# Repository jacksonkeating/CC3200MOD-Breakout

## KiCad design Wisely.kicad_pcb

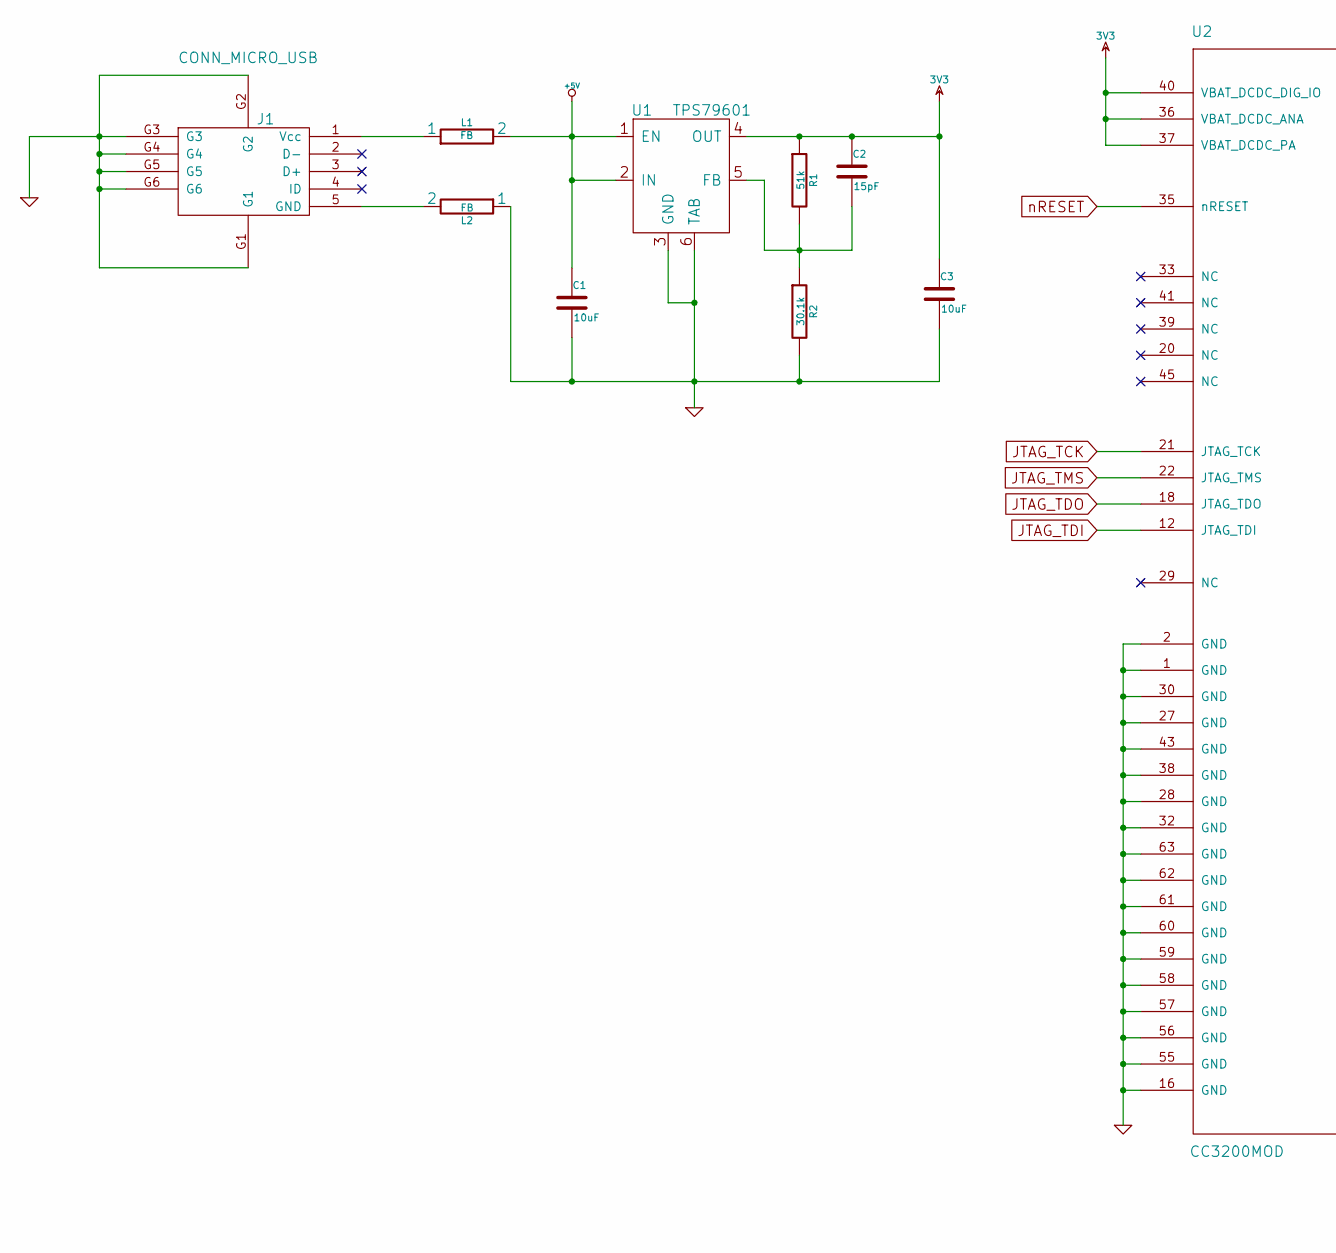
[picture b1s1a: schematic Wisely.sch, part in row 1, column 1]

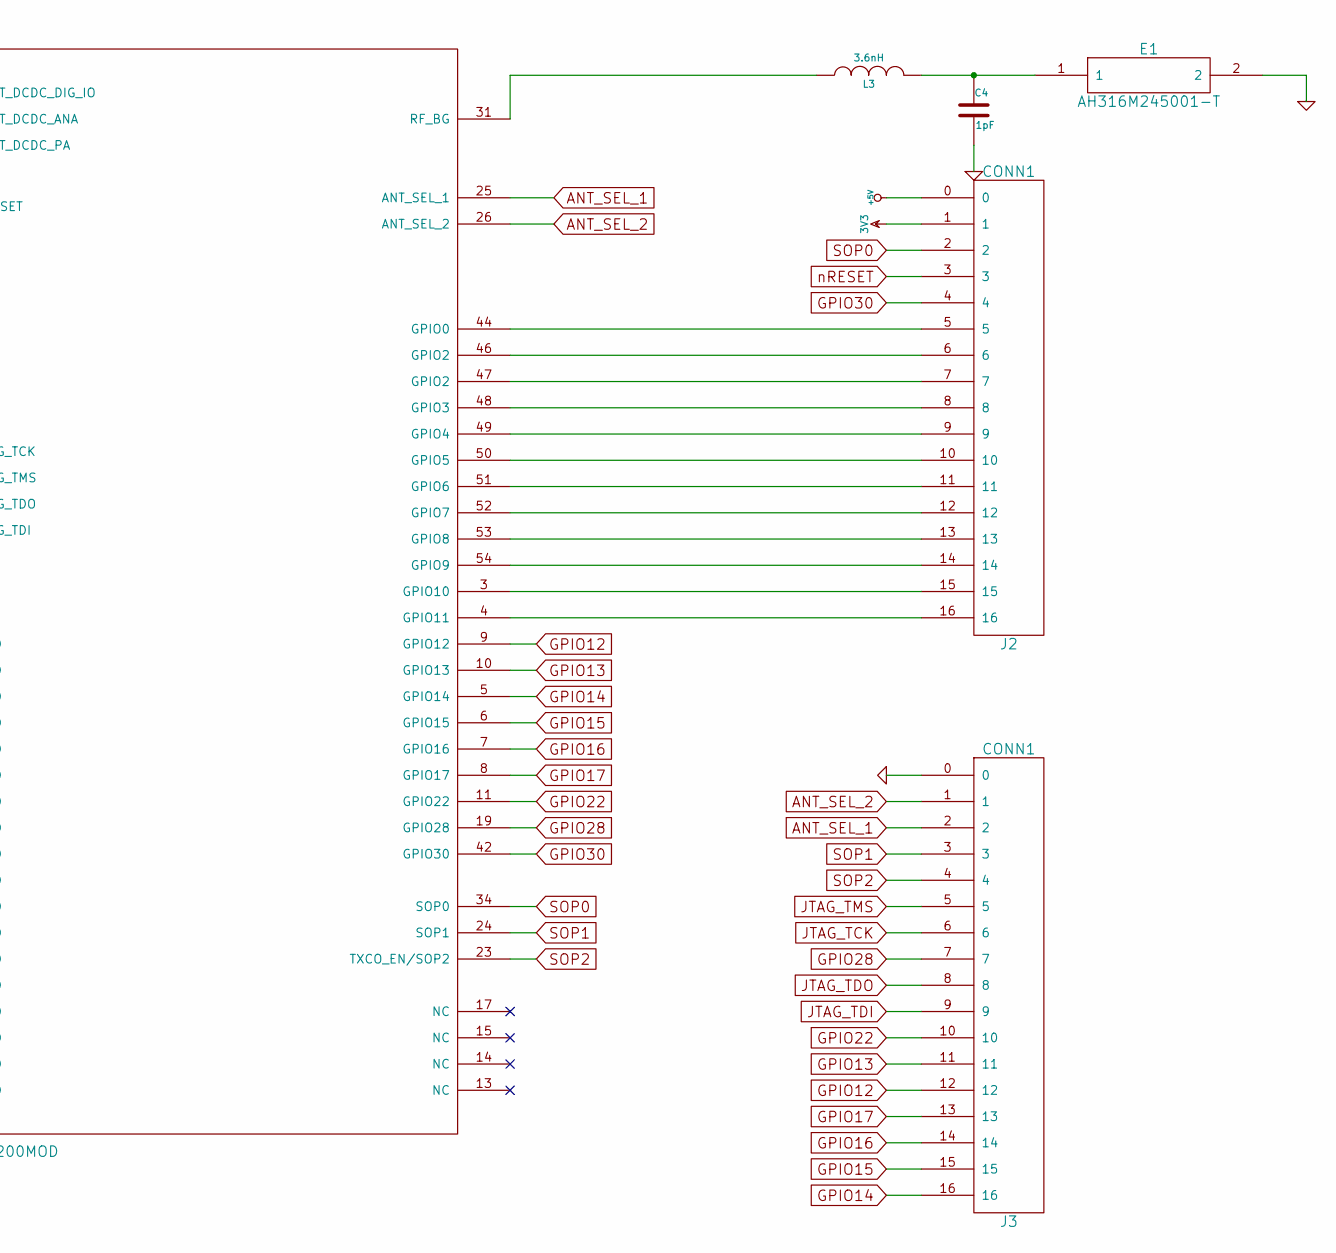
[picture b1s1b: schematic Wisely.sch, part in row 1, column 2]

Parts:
C1, C3: 10uF
C2: 15pF
C4: 1pF
E1: AH316M245001-T
J1: CONN_MICRO_USB
J2, J3: CONN1
L1, L2: FB
L3: 3.6nH
R1: 51k
R2: 30.1k
U1: TPS79601; Mfr_Part_Number TPS79601DCQR
U2: CC3200MOD

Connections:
3V3: C2.1, C3.1, J2.1, R1.1, U1.4 (OUT), U2.36 (VBAT_DCDC_ANA), U2.37 (VBAT_DCDC_PA), U2.40 (VBAT_DCDC_DIG_IO)
+5V: C1.1, J2.0, L1.2, U1.1 (EN), U1.2 (IN)
ANT_SEL_1: J3.2, U2.25 (ANT_SEL_1)
ANT_SEL_2: J3.1, U2.26 (ANT_SEL_2)
GND: C1.2, C3.2, C4.2, E1.2, J1.G1, J1.G2, J1.G3, J1.G4, J1.G5, J1.G6, J3.0, L2.1, R2.2, U1.3 (GND), U1.6 (TAB), U2.1 (GND), U2.2 (GND), U2.16 (GND), U2.27 (GND), U2.28 (GND), U2.30 (GND), U2.32 (GND), U2.38 (GND), U2.43 (GND), U2.55 (GND), U2.56 (GND), U2.57 (GND), U2.58 (GND), U2.59 (GND), U2.60 (GND), U2.61 (GND), U2.62 (GND), U2.63 (GND)
GPIO12: J3.12, U2.9 (GPIO12)
GPIO13: J3.11, U2.10 (GPIO13)
GPIO14: J3.16, U2.5 (GPIO14)
GPIO15: J3.15, U2.6 (GPIO15)
GPIO16: J3.14, U2.7 (GPIO16)
GPIO17: J3.13, U2.8 (GPIO17)
GPIO22: J3.10, U2.11 (GPIO22)
GPIO28: J3.7, U2.19 (GPIO28)
GPIO30: J2.4, U2.42 (GPIO30)
JTAG_TCK: J3.6, U2.21 (JTAG_TCK)
JTAG_TDI: J3.9, U2.12 (JTAG_TDI)
JTAG_TDO: J3.8, U2.18 (JTAG_TDO)
JTAG_TMS: J3.5, U2.22 (JTAG_TMS)
unnamed: J1.1 (Vcc), L1.1
unnamed: J1.5 (GND), L2.2
unnamed: C2.2, R1.2, R2.1, U1.5 (FB)
unnamed: L3.1, U2.31 (RF_BG)
unnamed: J2.7, U2.47 (GPIO2)
unnamed: J2.9, U2.49 (GPIO4)
unnamed: J2.8, U2.48 (GPIO3)
unnamed: J2.12, U2.52 (GPIO7)
unnamed: J2.11, U2.51 (GPIO6)
unnamed: J2.10, U2.50 (GPIO5)
unnamed: J2.14, U2.54 (GPIO9)
unnamed: J2.6, U2.46 (GPIO2)
unnamed: J2.5, U2.44 (GPIO0)
unnamed: J2.13, U2.53 (GPIO8)
unnamed: J2.16, U2.4 (GPIO11)
unnamed: J2.15, U2.3 (GPIO10)
unnamed: C4.1, E1.1, L3.2
SOP0: J2.2, U2.34 (SOP0)
SOP1: J3.3, U2.24 (SOP1)
SOP2: J3.4, U2.23 (TXCO_EN/SOP2)
nRESET: J2.3, U2.35 (nRESET)

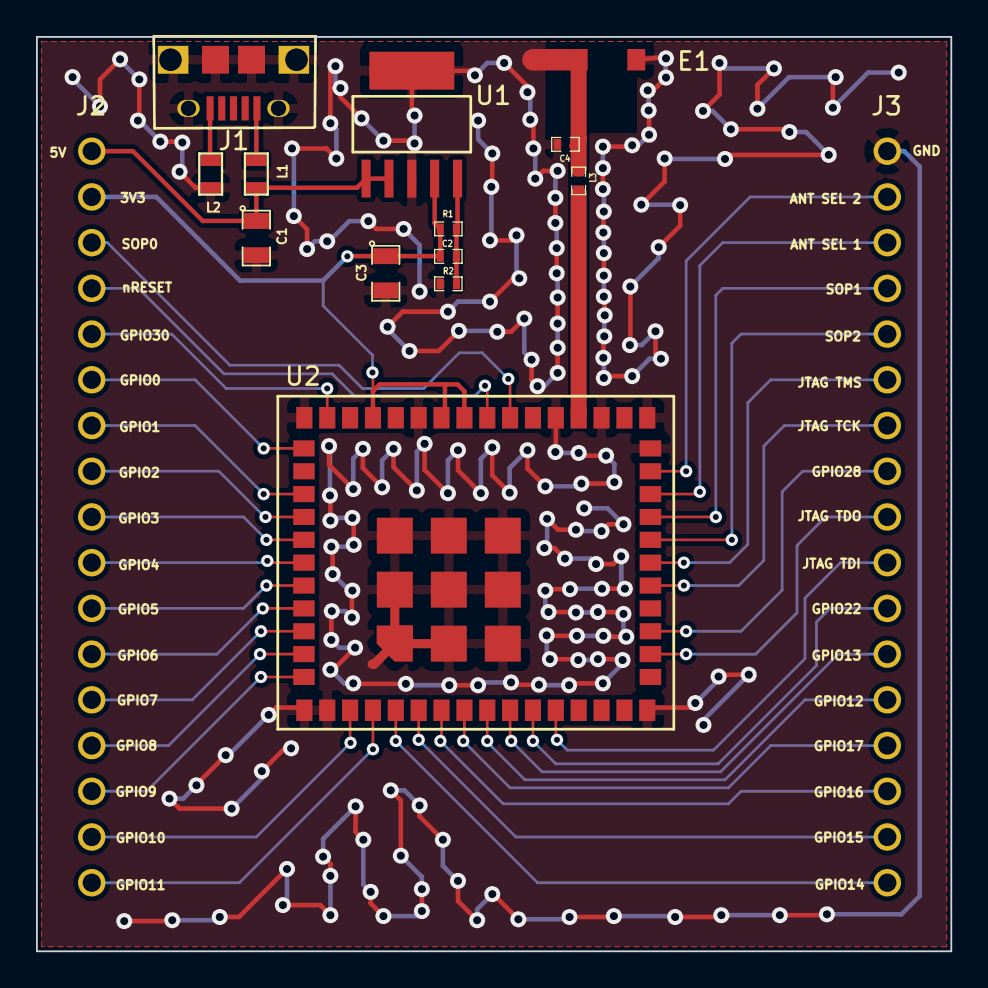
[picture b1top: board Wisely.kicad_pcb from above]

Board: 2 copper layers, 50.8 x 50.8 mm, 15 parts (0 on the bottom side), 39 nets.

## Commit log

2015-03-14 First commit
    Board is complete, but needs to be verified.
2015-03-16 Small corrections
    Added pin names to the silkscreen. Also added larger holes in the USB micro through-hole footprint. The previous revision had exact oval-type through holes, but it seems that some manufacturers won't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
2015-03-17 Wisely 0.0.3 Antenna trace correction
    Had to correct the antenna trace. The antenna pin 1 is not labeled as a ground pin. This should be corrected in the future because the application notes require that both the input pin and the ground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
